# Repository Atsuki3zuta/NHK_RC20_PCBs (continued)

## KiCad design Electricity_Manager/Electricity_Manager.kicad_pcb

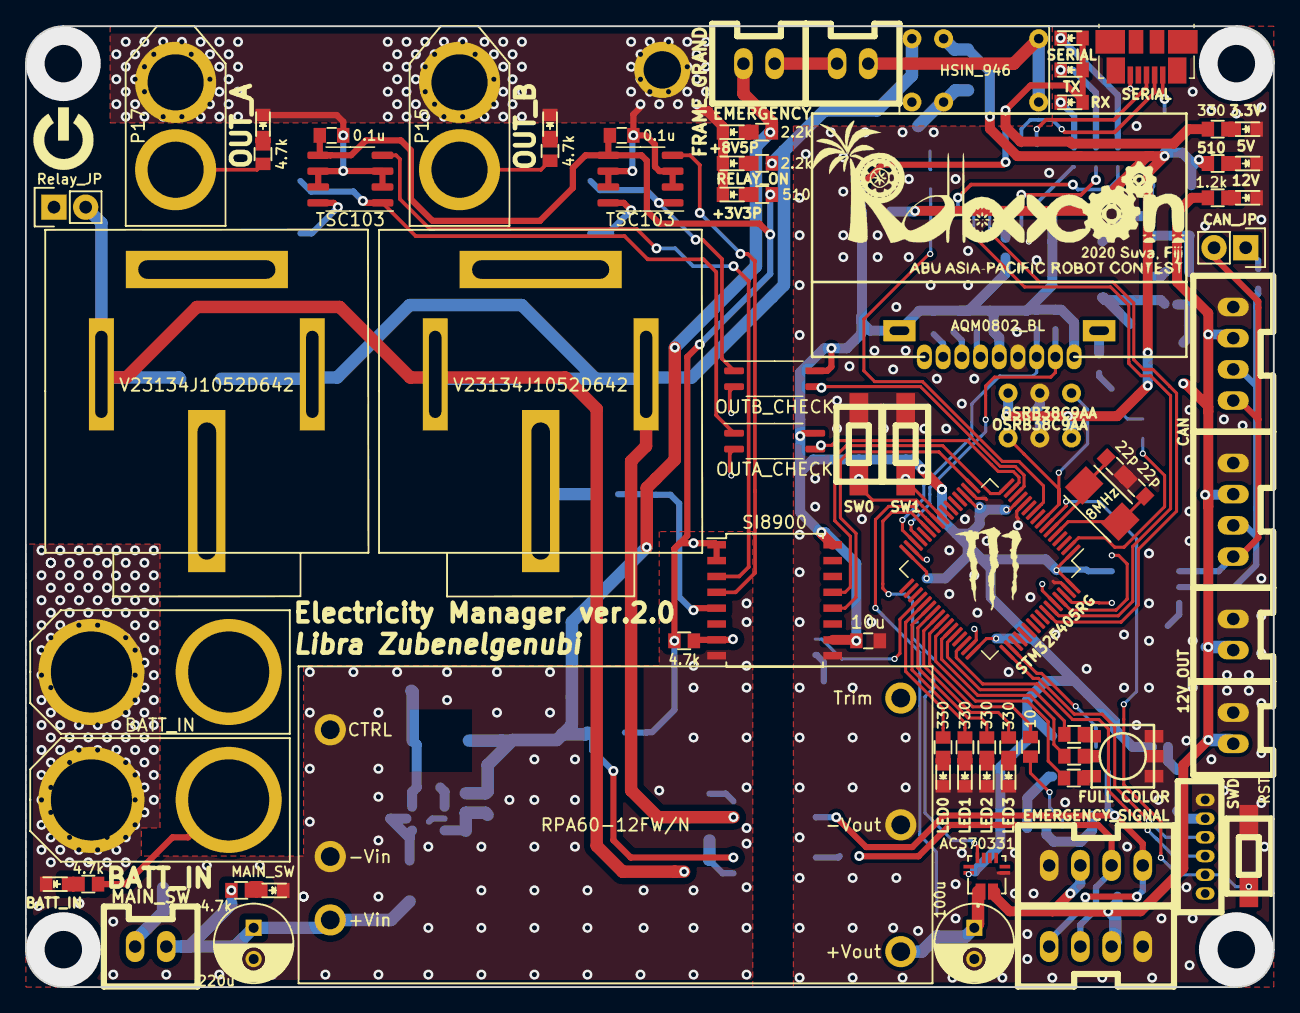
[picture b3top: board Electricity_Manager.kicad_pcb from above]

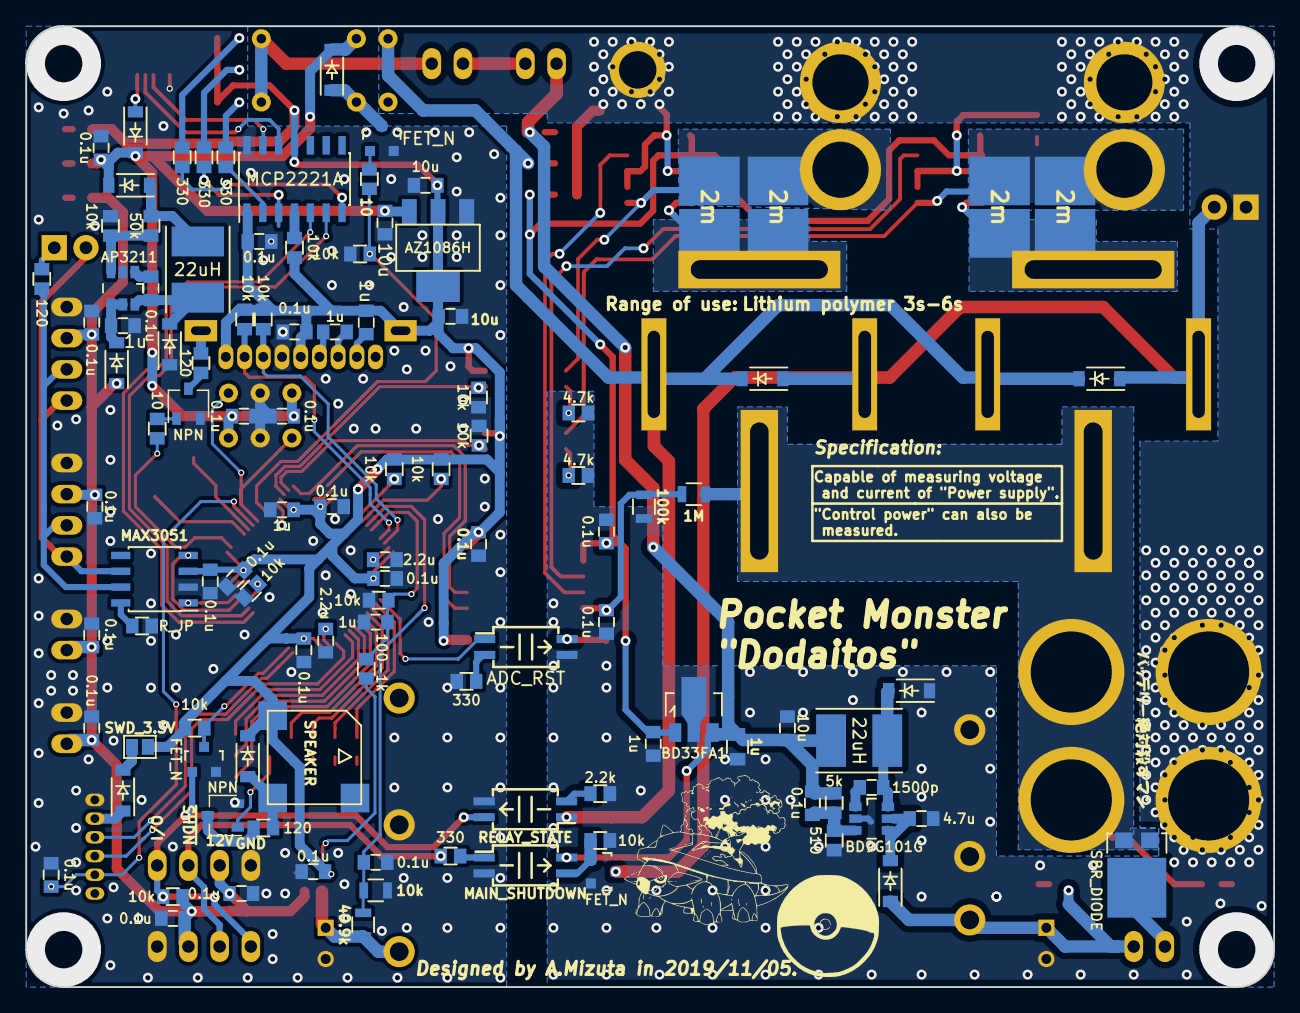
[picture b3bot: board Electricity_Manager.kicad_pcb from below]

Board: 2 copper layers, 100.0 x 77.0 mm, 195 parts (112 on the bottom side), 120 nets.

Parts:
AMP1, AMP2: TSC103; SO-8_3.9x4.9mm_P1.27mm
C1, C5: 22p; C_0603
C2, C3, C4, C6, C7, C8, C9, C10, C12, C14, C16, C17, C18, C19, C22, C23, C27, C29, C30, C33, C34, C38, C41, C44, C47, C48: 0.1u; C_0603
C11, C13: 2.2u; C_0603
C15, C20, C21, C25, C42, C43: 1u; C_0603
C24, C26, C28, C46, C49: 10u; C_0603
C31: 4.7u; C_0603
C32: 220u; C_Radial_D6.3_L11.2_P2.5
C35: 100u; C_Radial_D6.3_L11.2_P2.5
C36: 1500p; C_0603
C37: 1u; C_0805
D1, D9, D11, D12, D13, D21, D22, D23, D24, D25, D29: DIODE; SOD-123
D2: 12V; LED_0603
D3: 5V; LED_0603
D4: 3.3V; LED_0603
D5: LED0; LED_0603
D6: LED1; LED_0603
D7: LED2; LED_0603
D8: LED3; LED_0603
D10: SBR_DIODE; TO-277A
D14: BATT_IN; LED_0603
D15: MAIN_SW; LED_0603
D16: POWER_OUT; LED_0603
D17: FUN_OUT; LED_0603
D18: RELAY_ON; LED_0603
D19: +8V5P; LED_0603
D20: +3V3P; LED_0603
D26: RX; LED_0603
D27: TX; LED_0603
D28: SERIAL; LED_0603
IC2: MAIN_SHUTDOWN; SOIJ-4_5.3x5.3mm_Pitch1.27mm
IC3: RELAY_STATE; SOIJ-4_5.3x5.3mm_Pitch1.27mm
IC4: ADC_RST; SOIJ-4_5.3x5.3mm_Pitch1.27mm
J1: SERIAL; USB_Micro-B_Molex_47346-0001
JP1: Relay_JP; Pin_Header_Straight_1x02
JP2: SWD_3.3V; GS2
JP3: CAN_JP; Pin_Header_Straight_1x02
L1, L2: 22uH; Inductor_Taiyo-Yuden_NR-50xx_HandSoldering
P1: SWD; ZH_6T
P2, P3: CAN; XA_4T
P4, P5: EMERGENCY_SIGNAL; XA_4T
P6, P7: 12V_OUT; XA_2T
P9: MAIN_SW; XA_2T
P10, P11: EMERGENCY; XA_2T
P12: FRAME_GRAND; SolderWirePad_single_3mmDrill
P13, P16: BATT_IN; XT90PB
P15: OUT_B; XT60_F
P17: OUT_A; XT60_M
Q1, Q4, Q7: FET_N; SOT-23
Q2, Q3: NPN; SOT-23W
R1, R4, R5, R10, R13, R14, R15, R16, R19, R21, R25, R51, R58: 330; R_0603
R2: 1.2k; R_0603
R3, R39, R42: 510; R_0603
R6, R24, R29: 120; R_0603
R7, R8, R17, R18, R22, R23, R26, R27, R32, R40, R43, R49, R54, R59: 10k; R_0603
R11, R37, R38: 2.2k; R_0603
R12: R_JP; R_0603
R20, R28, R48: 10; R_0603
R30, R33, R34, R35, R36, R44, R50: 4.7k; R_0603
R31: 50k; R_0603
R41: 5k; R_0603
R45: 1M; R_0805
R46: 100k; R_0805
R47: 100-1k; R_0603
R52: 49.9k; R_0805
R53: 10k; R_0805
R55, R56, R57, R60: 2m; WSHP2818
SP1: SPEAKER; UGCT7525AN4
SW1: RST; SW_SPST_CK_RS282G05A3
SW2: SW0; SW_SPST_CK_RS282G05A3
SW3: SW1; SW_SPST_CK_RS282G05A3
U1: MAX3051; SOIC-8_3.9x4.9mm_Pitch1.27mm
U2: STM32F405RG; LQFP-64_10x10mm_P0.5mm
U3: FULL COLOR; OSTBABS4C2B
U4: AQM0802_BL; AQM0802_BackLight
U5: AP3211; TSOT-6-MK06A
U6: SI8900; SOIC-16_7.5x10.3mm_Pitch1.27mm
U7: AZ1086H
U8, U12: V23134J1052D642
U9: RPA60-12FW/N; RPA60-24xxSFW
U10: BD9G101G; TSOT-6-MK06A
U11: OUTA_CHECK; SOIC-4_4.55x2.6mm_P1.27mm
U13: ACS70331; ALLEGRO_ACS70331EESATR-005U3
U14: OUTB_CHECK; SOIC-4_4.55x2.6mm_P1.27mm
U15: BD33FA1; SOT89-3_Housing
U16: LOGO; Robocon2020_30.0x12.5_silk
U17: LOGO; Power_logo_Silk_5x5
U18: LOGO; Mini_Monster
U19: MCP2221A; SOIC-14_3.9x8.7mm_Pitch1.27mm
U20, U21: OSRB38C9AA
U22: HSIN_946; relay_HSINDA_Y14H
U23: LOGO; Battery_Killer_logo
U24: LOGO; Dodaitos_15x15_silk
U25: LOGO; MonsterBall_10x10_silk
X1: 8MHz; Crystal_SMD_5032_2Pads

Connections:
3V3: AMP1.5, AMP2.5, C22.2, C33.1, C34.1, C43.2, R30.1, R39.2, U6.1, U6.2, U15.1
+3.3V: C4.1, C8.2, C9.2, C10.2, C12.2, C15.2, C18.2, C19.1, C20.1, C26.1, C27.1, C28.1, C41.1, C49.1, D9.2, D26.1, D27.1, D28.1, JP2.2, R4.2, R22.1, R23.1, R26.2, R27.2, R54.2, R59.1, SP1.1, U1.3, U2.1, U2.13, U2.19, U2.32, U2.48, U2.64, U4.5, U4.9, U4.10, U6.10, U6.16, U7.2, U11.4, U13.12, U14.4, U19.1, U19.11
+5V: C24.1, C29.1, C47.1, C48.1, D13.2, D25.2, D29.2, R3.2, U7.3, U20.3, U21.3, U22.5
+8V: C30.2, C37.2, C46.1, IC2.4, L2.2, P10.1, R38.2, R41.1, U15.3
+12V: C2.1, C6.1, C7.1, C14.1, C16.1, C17.1, D12.1, P2.2, P3.2, P4.2, P5.2, P6.2, P7.2, R2.2, R17.2, U13.3, U13.4
+BATT: D10.1, D10.2, P13.2, P16.2, R33.2, R45.2, U8.30, U12.30
/24V: C32.1, D21.1, P9.2, R34.2, U9.1
/ADC12_IN8: C44.1, R52.1, R53.2, U2.26
/ADC12_IN9: C42.1, R43.1, R47.1, U2.27
/CAN1_RX: U1.4, U2.61
/CAN1_TX: U1.1, U2.62
/CAN_H: P2.3, P3.3, R6.1, U1.7
/CAN_L: JP3.2, P2.4, P3.4, U1.6
/Coil: D22.2, D23.2, IC3.1, R37.2, U8.85, U12.85, U22.4
/CoilReadPin_PA15: Q4.3, R54.1, U2.50
/D+: J1.3, U19.13
/D-: J1.2, U19.12
/FB: R31.1, R32.2, U5.3
/Fource_shutdown: P4.3, P5.3, R15.2
/I2C2_SCL: R26.1, U2.29, U4.8
/I2C2_SDA: R27.1, U2.30, U4.7
/OSC_IN: C1.1, U2.5, X1.1
/OSC_OUT: C5.1, U2.6, X1.2
/OUTA_Current: AMP1.4, U6.3
/OUTB_Current: AMP2.4, U6.4
/PA0: R49.2, U2.14, U14.3
/PA1: R40.2, U2.15, U11.3
/PB15: IC4.1, U2.36
/PC0: U2.8, U20.1, U21.1
/PC2: R18.2, R48.1, U2.10
/PC4: R23.2, SW3.2, U2.24
/PC5: R22.2, SW2.2, U2.25
/PC6: R10.1, U2.37
/PC7: R13.1, U2.38
/PC8: R14.1, U2.39
/PC9: R16.1, U2.40
/PC13: R28.2, U2.2
/Relay_Out: D22.1, D23.1, JP1.2, Q1.3, U8.86, U12.86
/Relay_state: IC3.4, P4.4, P5.4, Q4.1, R17.1
/SWCLK: P1.3, U2.49
/SWDIO: P1.4, U2.46
/TIM1_CH1: R20.2, U2.41
/TIM1_CH2: R21.1, U2.42
/TIM1_CH3: R5.1, U2.43
/TIM1_CH4: R1.1, U2.44
/To_CurrentA: AMP1.8, R55.1, R56.1, U8.87
/To_CurrentB: AMP2.8, R57.1, R60.1, U12.87
/USART1_RX: U2.59, U19.6
/USART1_TX: U2.58, U19.5
/USART2_RX: U2.17, U6.12
/USART2_TX: U2.16, U6.13
/Voltage: C38.1, R45.1, R46.2, U6.5
/~RST: C3.1, P1.5, SW1.1, U2.7
GND: C1.2, C2.2, C3.2, C4.2, C5.2, C6.2, C7.2, C8.1, C9.1, C10.1, C11.2, C12.1, C13.2, C14.2, C15.1, C16.2, C17.2, C18.1, C19.2, C24.2, C25.2, C26.2, C27.2, C28.2, C29.2, C35.2, C41.2, C42.2, C44.2, C47.2, C48.2, C49.2, D2.2, D3.2, D4.2, D5.2, D6.2, D7.2, D8.2, D11.1, IC2.2, IC3.3, J1.5, P1.1, P2.1, P3.1, P4.1, P5.1, P6.1, P7.1, Q2.2, Q3.2, Q4.2, Q7.2, R8.2, R12.2, R18.1, R25.1, R32.1, R40.1, R43.2, R49.1, R53.1, SW1.2, SW2.1, SW3.1, U1.2, U2.12, U2.18, U2.63, U3.4, U3.5, U3.6, U4.6, U5.2, U6.9, U7.1, U9.5, U13.5, U19.14, U20.2, U21.2
GNDPWR: AMP1.2, AMP1.3, AMP1.6, AMP1.7, AMP2.2, AMP2.3, AMP2.6, AMP2.7, C22.1, C31.2, C32.2, C33.2, C34.2, C37.1, C38.2, C43.1, C46.2, D14.2, D15.2, D16.2, D17.2, D18.2, D19.2, D20.2, D24.1, IC4.3, JP1.1, P12.1, P13.1, P15.1, P16.1, P17.1, Q1.2, R7.1, R11.1, R42.1, R44.1, R46.1, R50.1, U6.8, U9.2, U9.3, U10.2, U15.2
unnamed: C11.1, U2.31
unnamed: C13.1, U2.47
unnamed: C20.2, U4.2
unnamed: C21.1, U4.4
unnamed: C21.2, U4.3
unnamed: C23.1, D11.2, L1.1, U5.6
unnamed: C23.2, U5.1
unnamed: C25.1, D12.2, U5.4, U5.5
unnamed: C30.1, R41.2, R42.2, U10.3
unnamed: C31.1, D21.2, U10.4, U10.5
unnamed: C35.1, R52.2, U9.6, U13.1, U13.2
unnamed: C36.1, U10.1
unnamed: C36.2, D24.2, L2.1, U10.6
unnamed: D1.1, P1.2
unnamed: D1.2, JP2.1
unnamed: D2.1, R2.1
unnamed: D3.1, R3.1
unnamed: D4.1, R4.1
unnamed: D5.1, R10.2
unnamed: D6.1, R13.2
unnamed: D7.1, R14.2
unnamed: D8.1, R16.2
unnamed: D9.1, R24.2, SP1.2
unnamed: D10.3, P9.1
unnamed: D13.1, L1.2, R31.2
unnamed: D14.1, R33.1
unnamed: D15.1, R34.1
unnamed: D16.1, R35.1
unnamed: D17.1, R36.1
unnamed: D18.1, R37.1
unnamed: D19.1, R38.1
unnamed: D20.1, R39.1
unnamed: D25.1, Q7.3, U22.2
unnamed: D26.2, R19.1
unnamed: D27.2, R51.1
unnamed: D28.2, R58.1
unnamed: D29.1, J1.1
unnamed: IC2.1, R15.1
unnamed: IC2.3, Q1.1, R7.2
unnamed: IC3.2, R11.2
unnamed: IC4.2, R25.2
unnamed: IC4.4, R30.2, U6.7
unnamed: JP3.1, R6.2
unnamed: P10.2, P11.1
unnamed: P11.2, U22.1
unnamed: Q2.1, R20.1
unnamed: Q2.3, R24.1
unnamed: Q3.1, R28.1
unnamed: Q3.3, R29.1
unnamed: Q7.1, R48.2
unnamed: R1.2, U3.1
unnamed: R5.2, U3.2
unnamed: R8.1, U2.60
unnamed: R12.1, U1.8
unnamed: R19.2, U19.2
unnamed: R21.2, U3.3
unnamed: R29.2, U4.11
unnamed: R44.2, U11.2
unnamed: R47.2, U13.10
unnamed: R50.2, U14.2
unnamed: R51.2, U19.3
unnamed: R58.2, U19.7
unnamed: R59.2, U19.4
OUT_A: AMP1.1, P17.2, R35.2, R55.2, R56.2, U11.1
OUT_B: AMP2.1, P15.2, R36.2, R57.2, R60.2, U14.1
